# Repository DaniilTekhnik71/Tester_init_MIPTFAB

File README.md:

# Tester_init_MIPTFAB
ОПИСАНИЕ РАБОТЫ

1. При включении тестера без его подключения к гнезду USB, тестер переходит в режим измерения сопротивлений дата линий порта USB, при этом на экране надпись USB RESISTOR и перемигиваются светодиоды OK (зеленый) и BAD (красный), этот режим еще показывает, что обе линии оборваны при подключении его к порту USB

2. Дата лини проверяются по одной и вместе относительно земли, а так же между собой. Результат выводиться на экран:

- если все нормально - ОК, горит светодиод GOOD (зеленый)

- если одна из дата линий закорочена или имеет низкое сопротивление, меньше 200 Ом, то на экране надпись этой линии : -D или +D, загорается светодиод BAD(красный) и TX(желтый), если -D и RX(синий), если +D, а так же буззер кратко временно пищит

- если обе линии закорочены на землю или малое сопротивление, загораются светодиод BAD(красный) TX(желтый) RX(синий) , а так же буззер кратко временно пищит

- если одна из линий нормальная, а другая, оборвана или -D или +D, на экране -D>kOm или +D>kOm, загорается светодиод BAD(красный), мигает TX(желтый) или RX(синий), а так же буззер кратко временно пищит

- если обе линии закорочены между собой, на экране D-+, загорается светодиод BAD(красный), загораются светодиоды TX(желтый) и RX(синий), а так же буззер кратко временно пищит

3. Режим инициализации,производится тестером в выключеном состоянии,при подаче питания на USB тестер включается, светиться светодиод возле разъема USB +5V(зеленый)

- если инициализация прошла, то на экране надпись INIT OK, мигает светодиод OK (зеленый) и буззер кратко временно, один раз издает писк

- если инициализация не прошла, то NO INIT и моргает светодиод BAD(красный)

4. Заряд тестера происходит при подаче питания на USB 5V

не зависимо включен тестер или выключен

При заряде мигает светодиод CHARGE (зеленый) находится возле аккумулятора,по окончании заряда горит постоянно

При разряде аккумулятора горит светодиод DISCHARGE(красный) находится возле аккумулятора

5. Использованные компоненты:

                              Reference	  Value	  Footprint	                      	Qty
   
                             *R7,R1,R2	  100	    Resistor_SMD:R_0402_1005Metric	~	3
   
                              BZ1        	Buzzer	Buzzer_Beeper:MagneticBuzzer_PUI_AT-0927-TT-6-R	~	1
   
                              C*7	        *2.2uF	Capacitor_SMD:C_0402_1005Metric	~	1
   
                              C1,C6,C7	  10uF	  Capacitor_SMD:C_0603_1608Metric	~	3
   
                              C2,C5	      10uF	  Capacitor_SMD:C_1206_3216Metric		2
   	
                              C3,C8,C12  	0.1uF	  Capacitor_SMD:C_0402_1005Metric	~	3
   
                              C4,C9	      1uF	    Capacitor_SMD:C_0402_1005Metric	~	2
   
                              C10,C11	    22pF	  Capacitor_SMD:C_0402_1005Metric	~	2
   
                              D1	    LED CHARGE	LED_SMD:LED_0603_1608Metric	~	1
   
                              D2	    LED DISCHARGE	LED_SMD:LED_0603_1608Metric	~	1
   
                              D3	        VUSB	  LED_SMD:LED_0603_1608Metric	~	1
   
                              D4	      1N4148W	  Diode_SMD:D_SOD-123	https://www.vishay.com/docs/85748/1n4148w.pdf	1
   
                              D5	        SS34	  Diode_SMD:D_SOD-123	https://www.vishay.com/docs/88751/ss32.pdf	1
   
                              D6,D7	    -DATA_TX	LED_SMD:LED_0603_1608Metric	~	2
   
                              D8	      BAD	LED   SMD:LED_0603_1608Metric	~	1
   
                              D9	        OK	    LED_SMD:LED_0603_1608Metric	~	1
   
                              F1	      500mA	    Fuse:Fuse_1206_3216Metric	~	1
   
                              J1	      USB_A	    Connector_USB:USB_A_CNCTech_1001-011-01101_Horizontal	~	1

                              J2	        BAT    	Connector_Wire:SolderWire-0.1sqmm_1x02_P3.6mm_D0.4mm_OD1mm	~	1
   	
                              J3	    Conn_01x04_Pin	Connector_Molex:Molex_KK-254_AE-6410-04A_1x04_P2.54mm_Vertical	~	1
   
                              L1	        1R5	    Inductor_SMD:L_1206_3216Metric	~	1
   
                              R*7	        *1.5	  Resistor_SMD:R_0402_1005Metric	~	1
   
            R3,R4,R5,R6,R10,R11,R12,R13,R14,R15	      1K	    Resistor_SMD:R_0402_1005Metric	~	10		

                              R7	        4K7	    Resistor_SMD:R_0402_1005Metric	~	1			
                              
                              R8,R9	      22R	    Resistor_SMD:R_0402_1005Metric	~	2			
                              
                              R16	        200R	  Resistor_SMD:R_0402_1005Metric	~	1			
                              
                              SW1	      SW_SPDT_321	Connector_Molex:Molex_KK-254_AE-6410-03A_1x03_P2.54mm_Vertical	~	1			
                              
                              U1	    ATmega32U4-M	Package_DFN_QFN:QFN-44-1EP_7x7mm_P0.5mm_EP5.2x5.2mm	http://ww1.microchip.com/downloads/en/DeviceDoc/Atmel-7766-8-bit-AVR-ATmega16U4-32U4_Datasheet.pdf	1		
                              
                              U2	        TP4333	Package_SO:SOP-8_3.9x4.9mm_P1.27mm		1			
                              
                              Y1	        16MHz	  Crystal:Crystal_SMD_0603-4Pin_6.0x3.5mm	https://foxonline.com/wp-content/uploads/pdfs/T5HN_T5HV.pdf	1
                              
6. Использованные инструменты: Паяльная станция с жалом типа "топорик", жало для пайки SMD типа C245-IS, паяльный фен 858D+, блок питания лабораторный KORAD 3005, осциллограф RIGOL, фрезерный станок CHARLY4U, система лазерной маркировки MINIMARKER2, пинцеты, припой ПОС61, флюс NC559, скальпель, изопропанол, жилы кабеля МГТФ.

7. Пррблемы и трудности: Из-за малых габаритов устройства метод фрезерования оказался неэффективным, толщины дорожек слишком малы и их изготовление не может быть обеспечено ручной настройкой и точностью фрезерного станка. После первой и последней успешной попытки
изготовления платы, стало понятно, что плата оказалоась отзеркаленной. Дальнейшие попытки фрезерования не увенчались успехом. Были попытки изготовление на лазерном станке MINIMARKER2, которые так же оказались неудачными, вследствие термического искривления
обрабатываемой платы и следовтельно, изменнеия фокусного расстояниря в процессе гравировки. Впоследсвтии было приянто решение производить COB монтаж элементов на отзеркаленную плату. По итогам монтажа выяснилось, что некоторые функции тестера работают некорректно,
такие как проверка инициализации, нет общения и определения заниженных значений сопротивлений на одной из DATA линий, хотя работоспособность платы была проверена на плате, заказанной на сайте Резонита. В настоящее фремя удалось исправить определение кз или заниженного сопротивления на одной из двух DATA линий, так же переход в режим инициализации, но по прежнему общения с компьютером нет.

  устройство с платой РЕЗОНИТ
  устройство на фрезерованной плате вид снизу
  устройство на фрезерованной плате вид сверху

ДЕМОНСТРАЦИИ РАБОТЫ УСТРОЙСТВА НА РАЗНЫХ ПЛАТАХ 

Плата Резонит Режим инициализации

https://github.com/user-attachments/assets/325fc64f-16dd-4dcc-aebc-f22ac2b17836

Плата Резонит Режил проверки линий

https://github.com/user-attachments/assets/79fad83d-0645-4a04-acb9-413c7f19cf63

Плата Фабрика Режим инициализации и проверки линий

https://github.com/user-attachments/assets/3a48dc3f-1959-441d-91f1-0622a66661fc

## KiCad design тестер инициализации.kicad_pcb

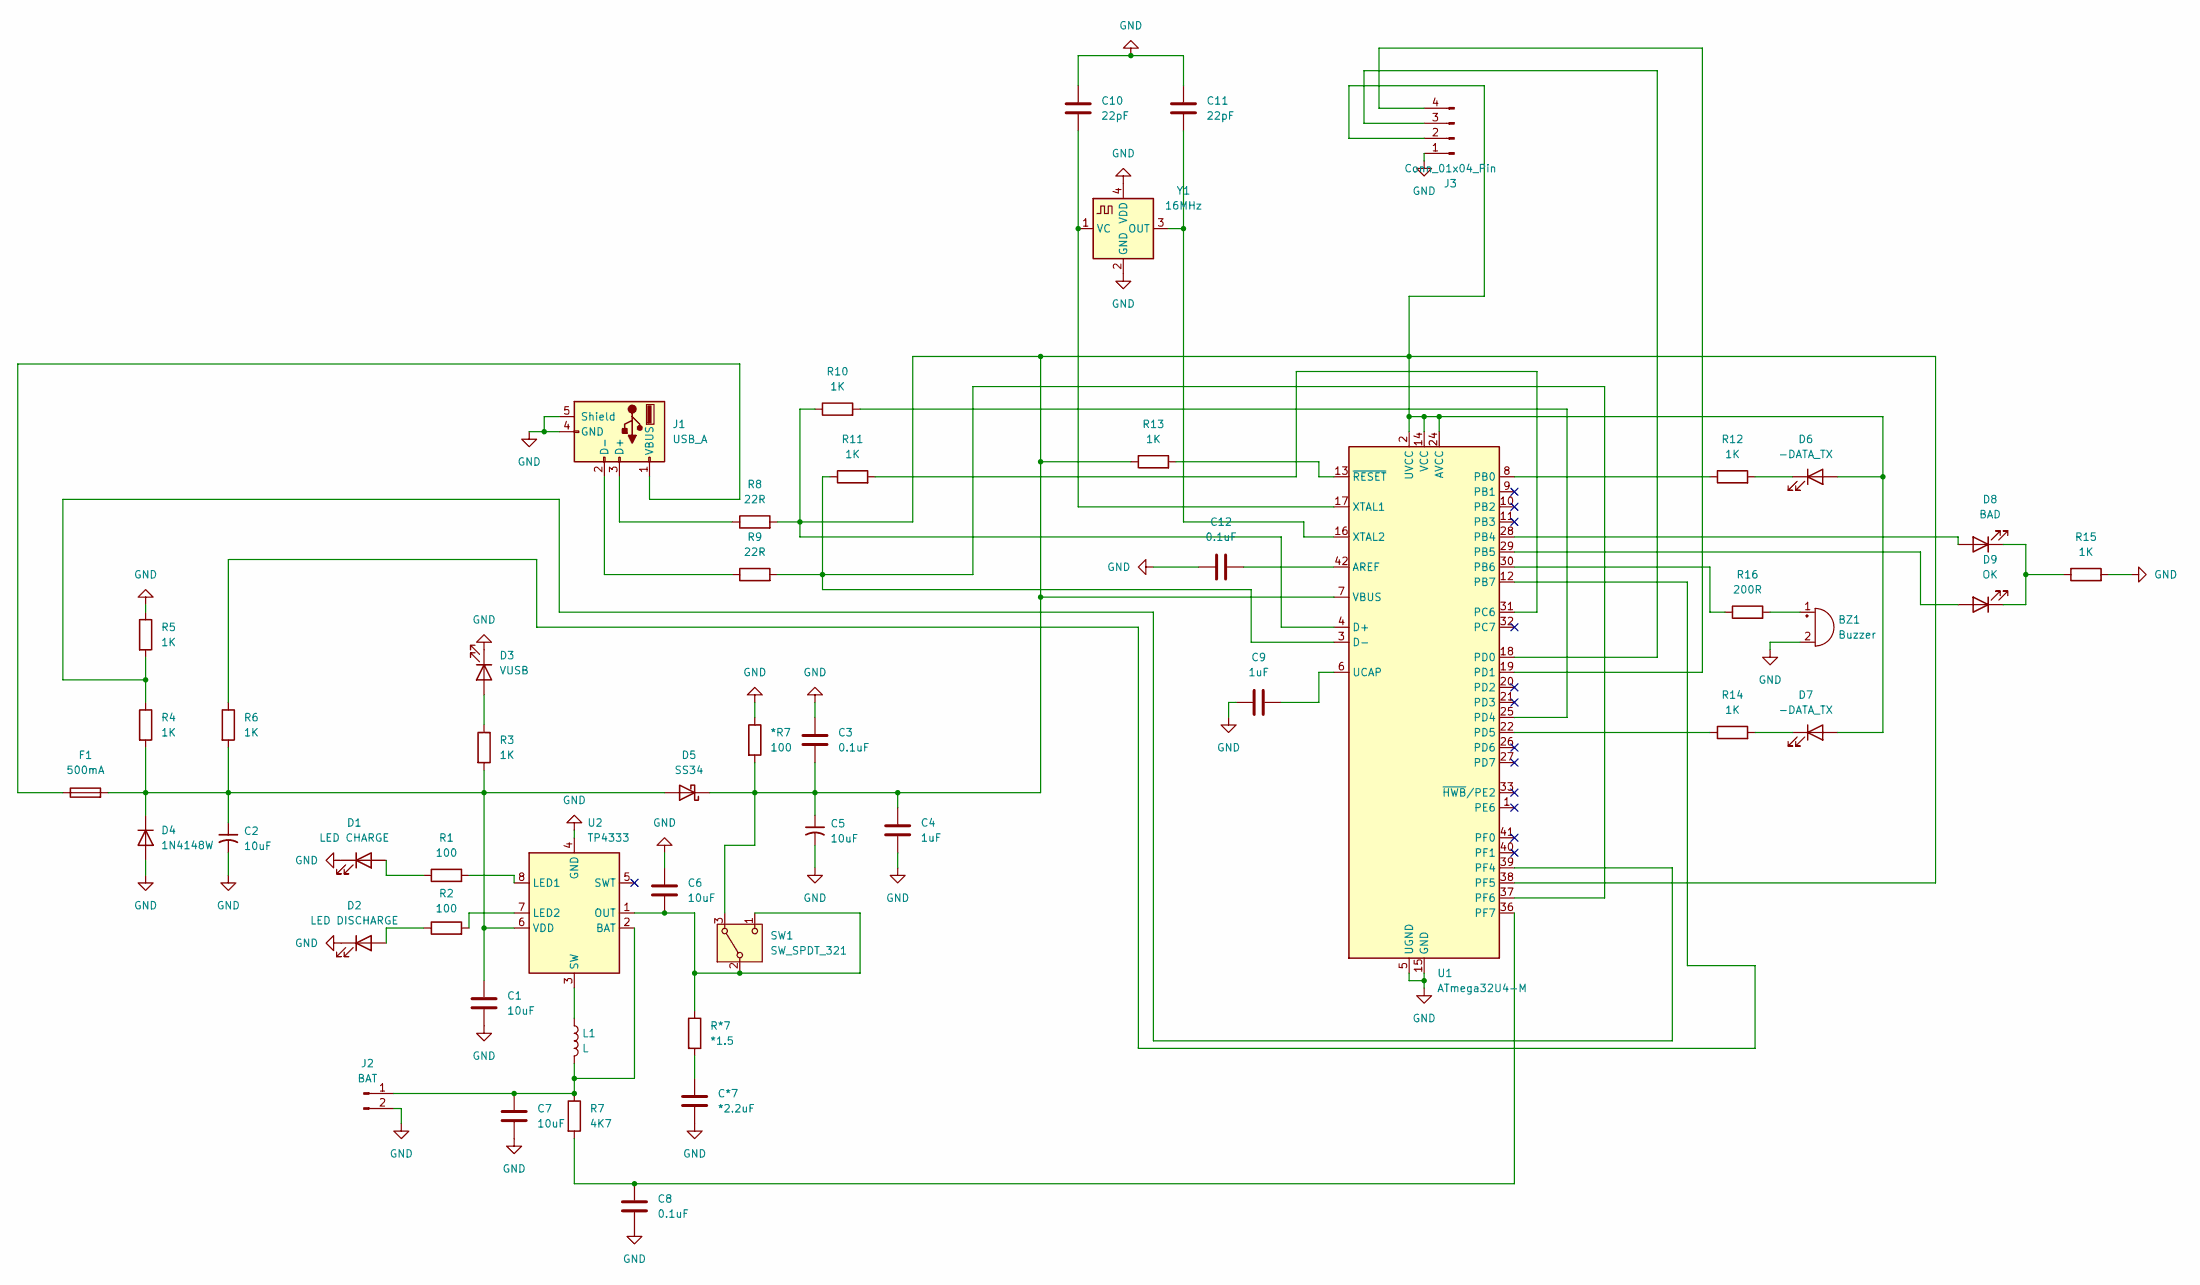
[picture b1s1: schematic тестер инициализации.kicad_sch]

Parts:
*R7: 100; R_0402_1005Metric
BZ1: Buzzer; MagneticBuzzer_PUI_AT-0927-TT-6-R
C1, C6, C7: 10uF; C_0603_1608Metric
C2, C5: 10uF; C_1206_3216Metric
C3, C8, C12: 0.1uF; C_0402_1005Metric
C4, C9: 1uF; C_0402_1005Metric
C10, C11: 22pF; C_0402_1005Metric
C*7: *2.2uF; C_0402_1005Metric
D1: LED CHARGE; LED_0603_1608Metric
D2: LED DISCHARGE; LED_0603_1608Metric
D3: VUSB; LED_0603_1608Metric
D4: 1N4148W; D_SOD-123
D5: SS34; D_SOD-123
D6, D7: -DATA_TX; LED_0603_1608Metric
D8: BAD; LED_0603_1608Metric
D9: OK; LED_0603_1608Metric
F1: 500mA; Fuse_1206_3216Metric
J1: USB_A; USB_A_CNCTech_1001-011-01101_Horizontal
J2: BAT; SolderWire-0.1sqmm_1x02_P3.6mm_D0.4mm_OD1mm
J3: Conn_01x04_Pin; Molex_KK-254_AE-6410-04A_1x04_P2.54mm_Vertical
L1: L; L_1206_3216Metric
R1, R2: 100; R_0402_1005Metric
R3, R4, R5, R6, R10, R11, R12, R13, R14, R15: 1K; R_0402_1005Metric
R7: 4K7; R_0402_1005Metric
R8, R9: 22R; R_0402_1005Metric
R16: 200R; R_0402_1005Metric
R*7: *1.5; R_0402_1005Metric
SW1: SW_SPDT_321; Molex_KK-254_AE-6410-03A_1x03_P2.54mm_Vertical
U1: ATmega32U4-M; QFN-44-1EP_7x7mm_P0.5mm_EP5.2x5.2mm
U2: TP4333; SOP-8_3.9x4.9mm_P1.27mm
Y1: 16MHz; Crystal_SMD_0603-4Pin_6.0x3.5mm

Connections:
GND: *R7.1, BZ1.2 (-), C1.2, C2.2, C3.1, C4.2, C5.2, C6.1, C7.2, C8.2, C9.1, C10.1, C11.1, C12.1, C*7.2, D1.1 (K), D2.1 (K), D3.1 (K), D4.2 (A), J1.4 (GND), J1.5 (Shield), J2.2, J3.1, R5.1, R15.2, U1.5 (UGND), U1.15 (GND), U1.23 (GND), U1.35 (GND), U1.43 (GND), U1.45 (GND), U2.4 (GND), Y1.2 (GND), Y1.4 (VDD)
unnamed: BZ1.1 (+), R16.2
unnamed: C*7.1, R*7.2
unnamed: D1.2 (A), R1.1
unnamed: D2.2 (A), R2.1
unnamed: D3.2 (A), R3.1
unnamed: C1.1, C2.1, D4.1 (K), D5.2 (A), F1.2, R3.2, R4.2, R6.2, U2.6 (VDD)
unnamed: *R7.2, C3.2, C4.1, C5.1, D5.1 (K), D6.2 (A), D7.2 (A), J3.2, R8.2, R10.1, R13.1, SW1.3 (A), U1.2 (UVCC), U1.4 (D+), U1.7 (VBUS), U1.14 (VCC), U1.24 (AVCC), U1.34 (VCC), U1.38 (PF5), U1.44 (AVCC)
unnamed: D6.1 (K), R12.2
unnamed: D7.1 (K), R14.2
unnamed: D8.2 (A), U1.28 (PB4)
unnamed: D8.1 (K), D9.1 (K), R15.1
unnamed: D9.2 (A), U1.29 (PB5)
unnamed: J1.3 (D+), R8.1
unnamed: J1.2 (D-), R9.1
unnamed: F1.1, J1.1 (VBUS)
unnamed: C7.1, J2.1, L1.2, R7.1, U2.2 (BAT)
unnamed: J3.3, U1.18 (PD0)
unnamed: J3.4, U1.19 (PD1)
unnamed: C6.2, R*7.1, SW1.1 (C), SW1.2 (B), U2.1 (OUT)
unnamed: C12.2, U1.42 (AREF)
unnamed: R9.2, R11.1, U1.3 (D-), U1.37 (PF6)
unnamed: R12.1, U1.8 (PB0)
unnamed: R16.1, U1.30 (PB6)
unnamed: R6.1, U1.12 (PB7)
unnamed: R11.2, U1.31 (PC6)
unnamed: R10.2, U1.25 (PD4)
unnamed: R14.1, U1.22 (PD5)
unnamed: R4.1, R5.2, U1.39 (PF4)
unnamed: C8.1, R7.2, U1.36 (PF7)
unnamed: C9.2, U1.6 (UCAP)
unnamed: C10.2, U1.17 (XTAL1), Y1.1 (VC)
unnamed: C11.2, U1.16 (XTAL2), Y1.3 (OUT)
unnamed: R13.2, U1.13 (~RESET)
unnamed: R1.2, U2.8 (LED1)
unnamed: R2.2, U2.7 (LED2)
unnamed: L1.1, U2.3 (SW)

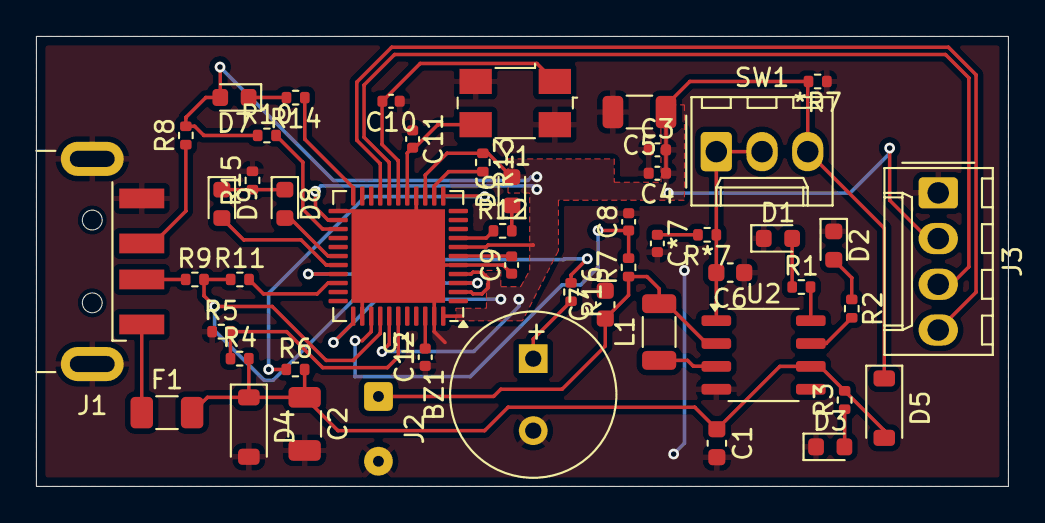
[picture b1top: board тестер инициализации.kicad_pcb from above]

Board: 2 copper layers, 54.0 x 25.0 mm, 50 parts (0 on the bottom side), 37 nets.
